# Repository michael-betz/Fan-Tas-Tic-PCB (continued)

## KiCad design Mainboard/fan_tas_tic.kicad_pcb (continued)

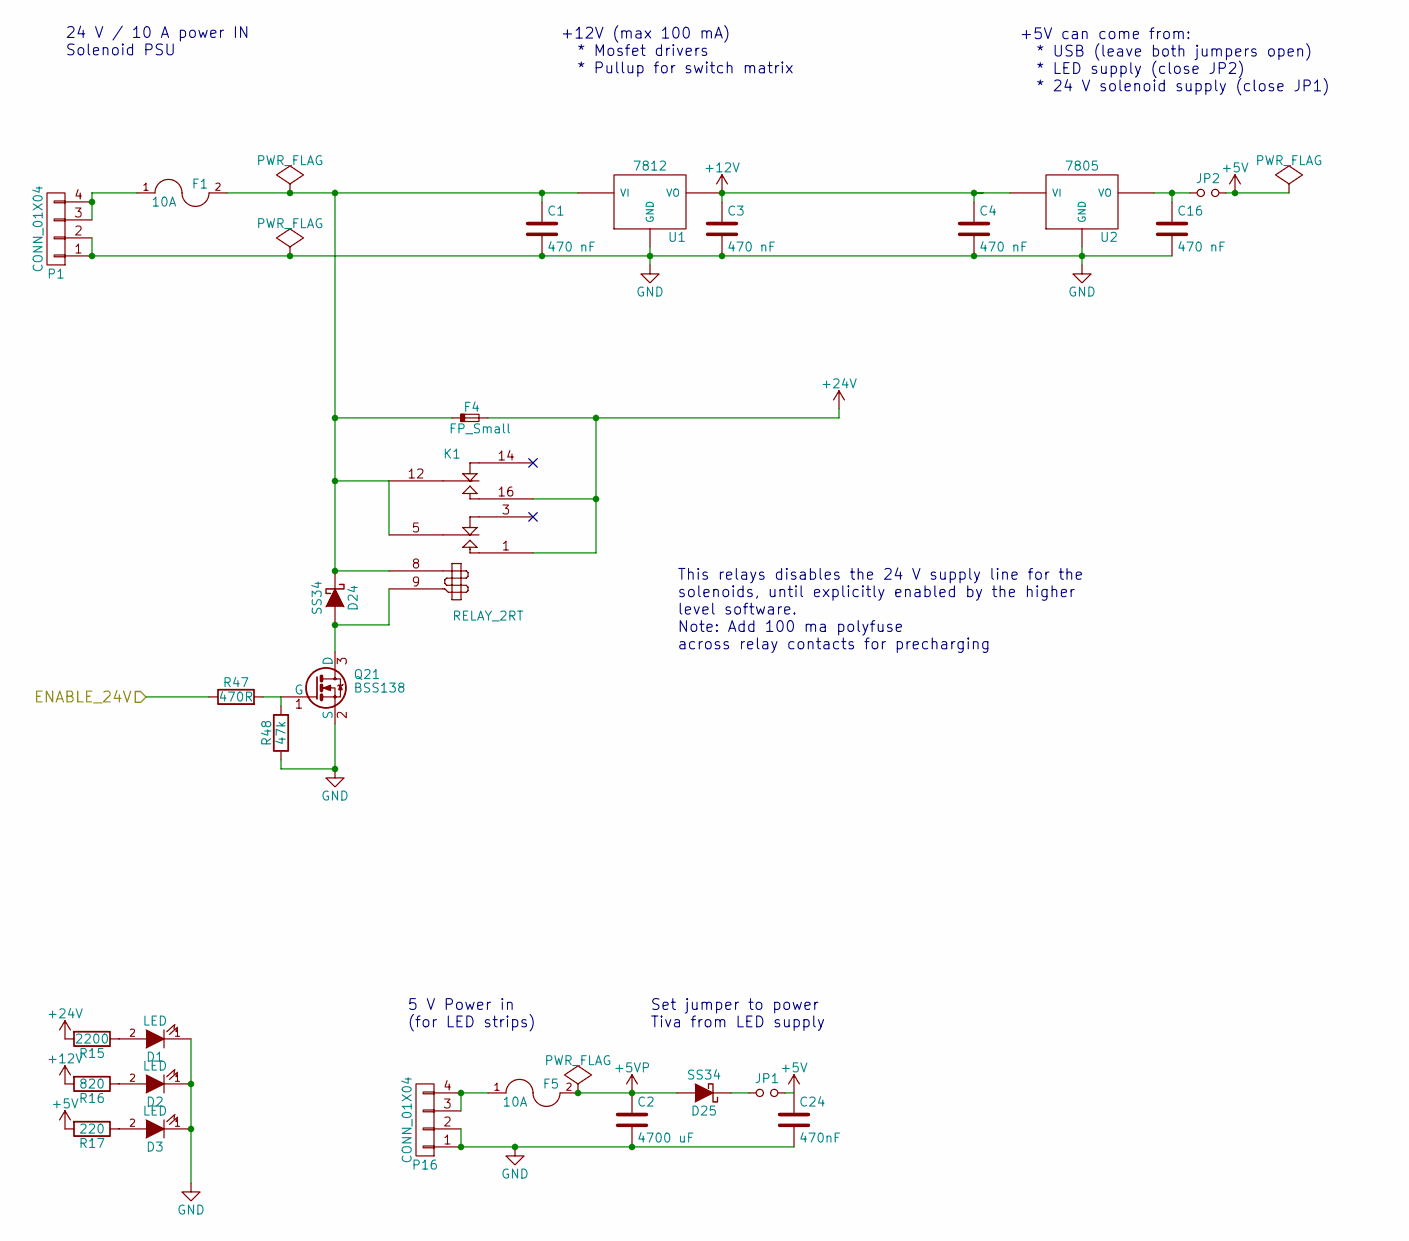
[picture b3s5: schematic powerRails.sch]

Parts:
C1, C3, C4, C16: 470 nF; C_0805_HandSoldering
C2: 4700 uF; C_Radial_D10_L16_P5
C24: 470nF; C_0805_HandSoldering
D1, D2, D3: LED; LED-0805
D24, D25: SS34; SMC-RM10_Universal_Handsoldering
F1, F5: 10A; Fuseholder5x20_horiz_open_universal_Type-III
F4: FP_Small; Fuse_SMD1206_HandSoldering
JP1, JP2: Jumper_NO_Small; Pin_Header_Straight_1x02
K1: RELAY_2RT; Relay_SPDT_RM5mm
P1, P16: CONN_01X04; HT396_4
Q21: BSS138; SOT-23
R15: 2200; R_0805_HandSoldering
R16: 820; R_0805_HandSoldering
R17: 220; R_0805_HandSoldering
R47: 470R; R_0805_HandSoldering
R48: 47k; R_0805_HandSoldering
U1: 7812; TO-220_Neutral123_Vertical_LargePads
U2: 7805; TO-220_Neutral123_Vertical_LargePads

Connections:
+5V: C24.1, JP1.2, JP2.2, R17.2; also elsewhere on the board
+5VP: C2.1, D25.2 (A), F5.2; also elsewhere on the board
+12V: C3.1, C4.1, R16.2, U1.VO, U2.VI; also elsewhere on the board
+24V: F4.2, K1.1 (T1), K1.16 (T2), R15.2; also elsewhere on the board
/PowerRails/ENABLE_24V: R47.1; also elsewhere on the board
GND: C1.2, C2.2, C3.2, C4.2, C16.2, C24.2, D1.1 (K), D2.1 (K), D3.1 (K), P1.1, P1.2, P16.1, P16.2, Q21.2 (S), R48.1, U1.GND, U2.GND; also elsewhere on the board
unnamed: C1.1, D24.1 (K), F1.2, F4.1, K1.5 (C1), K1.8, K1.12 (C2), U1.VI
unnamed: C16.1, JP2.1, U2.VO
unnamed: D1.2 (A), R15.1
unnamed: D2.2 (A), R16.1
unnamed: D3.2 (A), R17.1
unnamed: D24.2 (A), K1.9, Q21.3 (D)
unnamed: D25.1 (K), JP1.1
unnamed: F1.1, P1.3, P1.4
unnamed: F5.1, P16.3, P16.4
unnamed: Q21.1 (G), R47.2, R48.2

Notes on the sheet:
24 V / 10 A power IN Solenoid PSU
+5V can come from: * USB (leave both jumpers open) * LED supply (close JP2) * 24 V solenoid supply (close JP1)
5 V Power in (for LED strips)
Set jumper to power Tiva from LED supply
This relays disables the 24 V supply line for the solenoids, until explicitly enabled by the higher level software. Note: Add 100 ma polyfuse across relay contacts for precharging
+12V (max 100 mA) * Mosfet drivers * Pullup for switch matrix

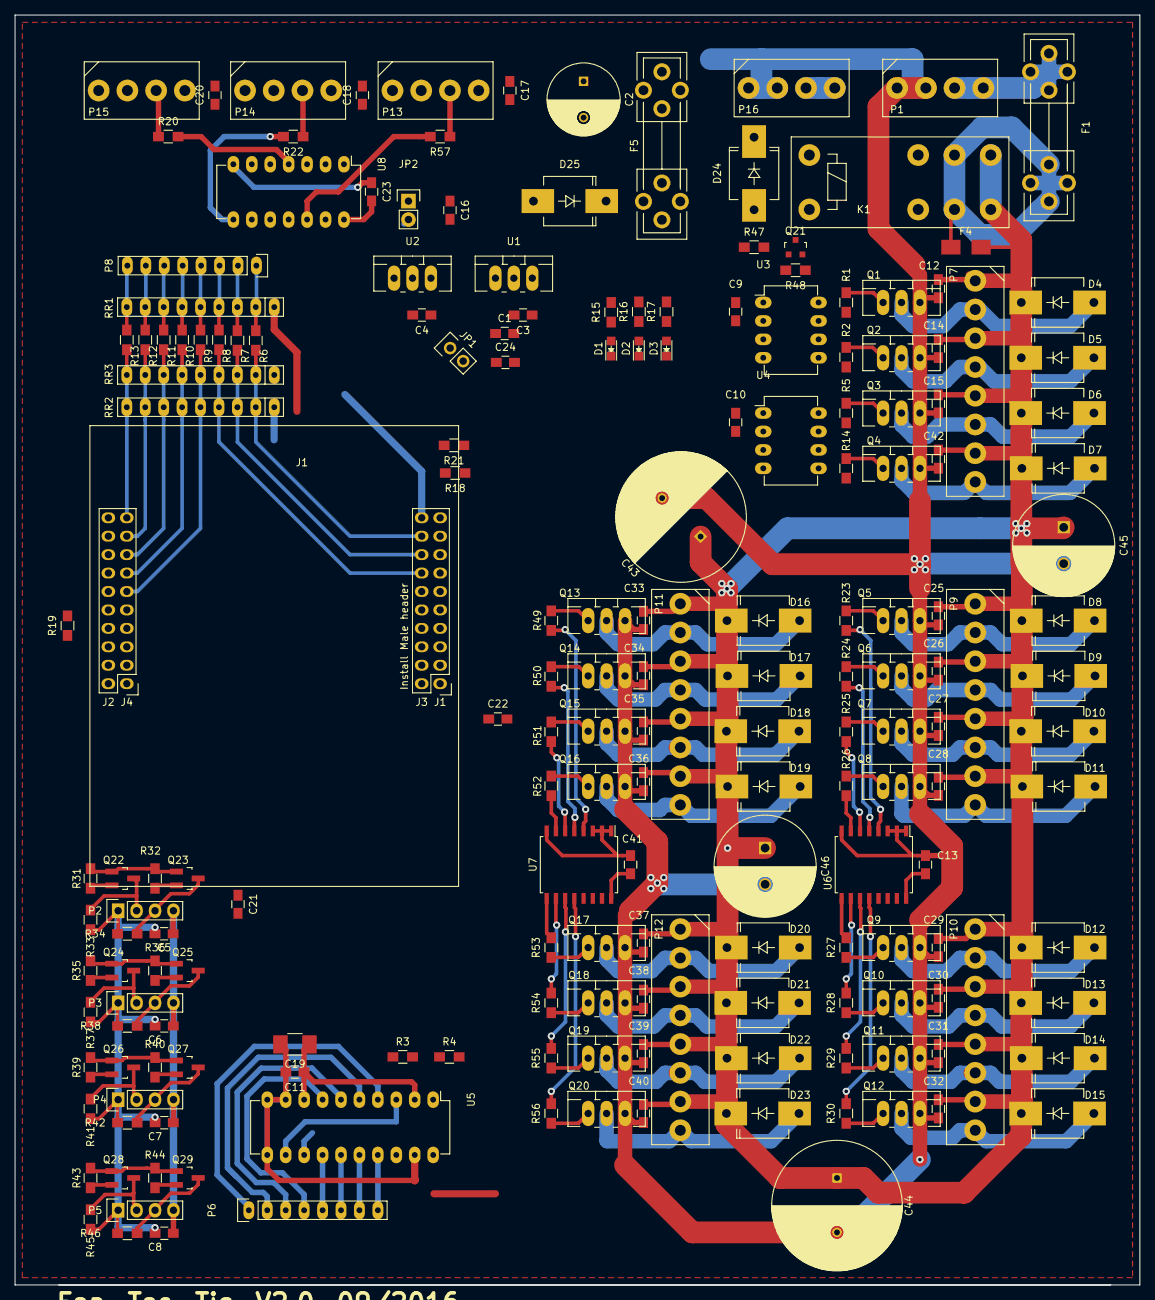
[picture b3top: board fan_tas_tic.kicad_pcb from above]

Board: 2 copper layers, 155.0 x 175.0 mm, 191 parts (0 on the bottom side), 135 nets.

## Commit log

2015-12-30 initial mainboard import
2015-12-31 Added Input and output extension templates
2016-01-04 Added the Input extension PCB layout
2016-01-06 Made space for TM4C123 USB connector
2016-01-13 Still Missing WS2811 level shifter
2016-01-16 Added 74HC04 buffer to WS2811 outputs
2016-01-17 Separated Tiva 5V from Power 5 V
2016-01-17 Larger pads and vias to allow some alignment error
2016-01-17 Docu cosmetics
2016-01-19 Cleaned up traces
2016-02-28 Small documentation updates
2016-06-12 Updated Schematic with minor changes after first prototype
2016-06-25 Started to work on Rev2
2016-06-26 Made I2C level converters more neat
2016-07-17 Added 8 additional Mosfet channels, cleaned up rouing a bit
2016-07-17 Updated README:
2018-11-14 Output extension looks good. Diodes still missing
2018-11-14 Add diodes
2018-11-14 Output extension ready for fab
2018-11-14 .4 mm traces
2018-11-16 Fabbed version
2018-12-14 Input extension 2
2018-12-14 Add new input extension pcb
2018-12-14 Doc!
2018-12-14 cleanup redundant doc files
2018-12-14 silkscreen
2018-12-17 Output extension: chunkier freewheelingdiode
